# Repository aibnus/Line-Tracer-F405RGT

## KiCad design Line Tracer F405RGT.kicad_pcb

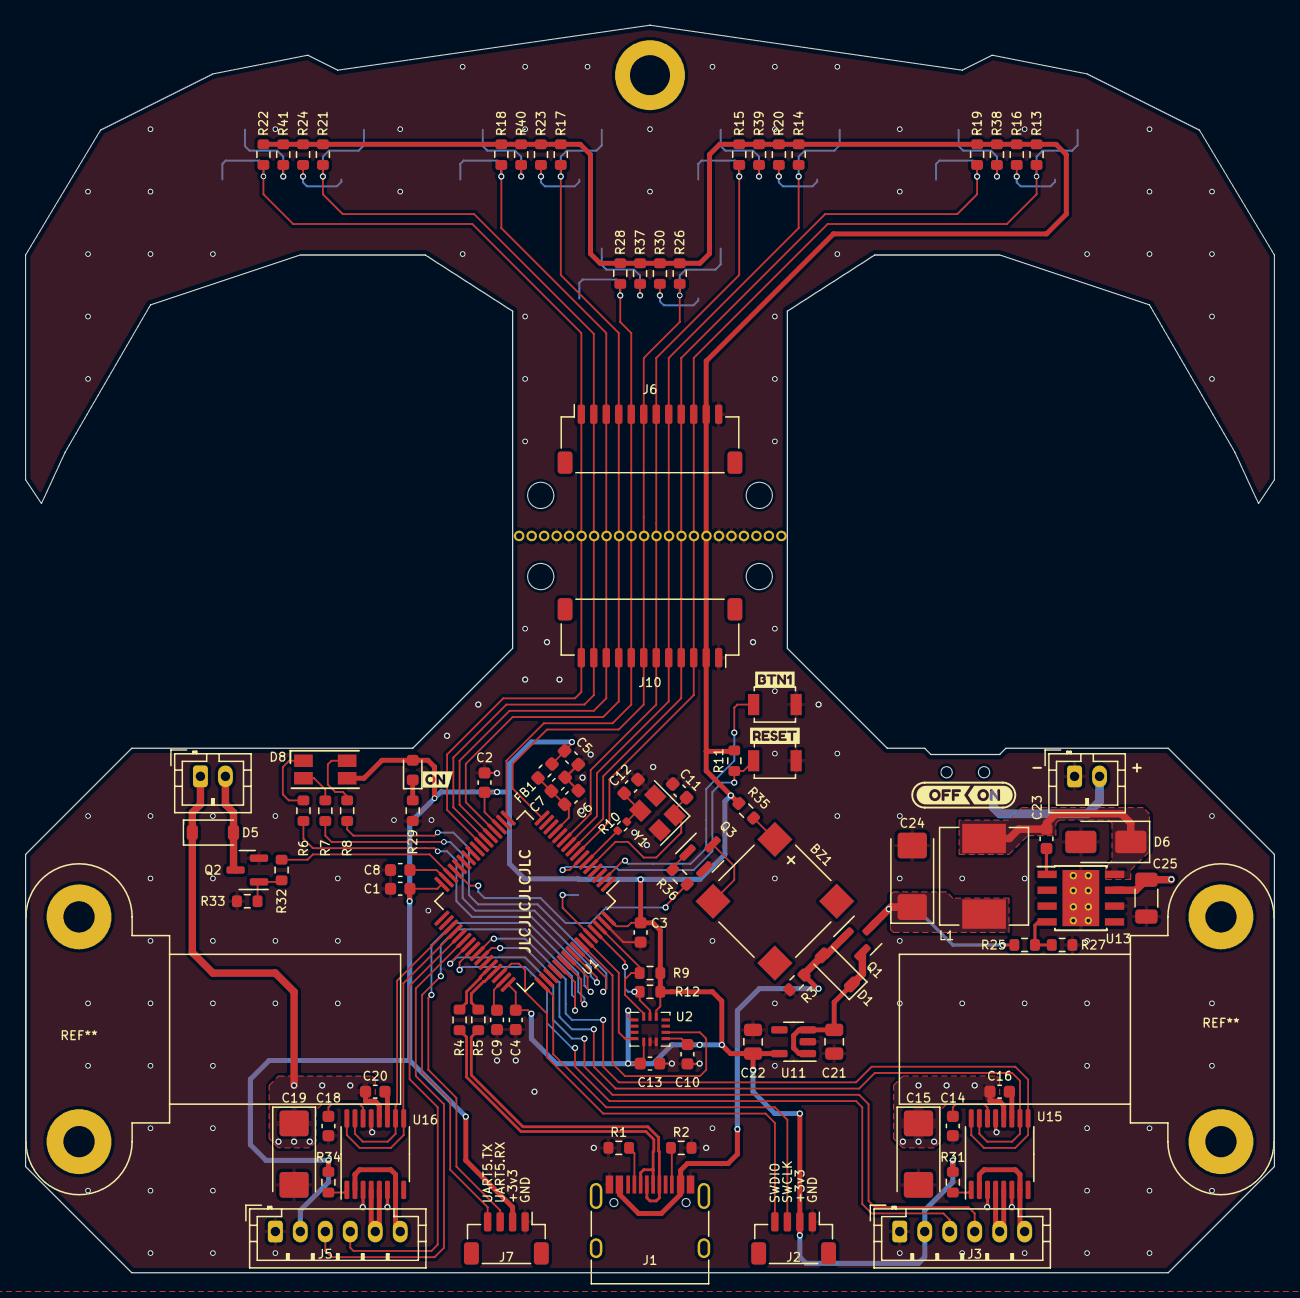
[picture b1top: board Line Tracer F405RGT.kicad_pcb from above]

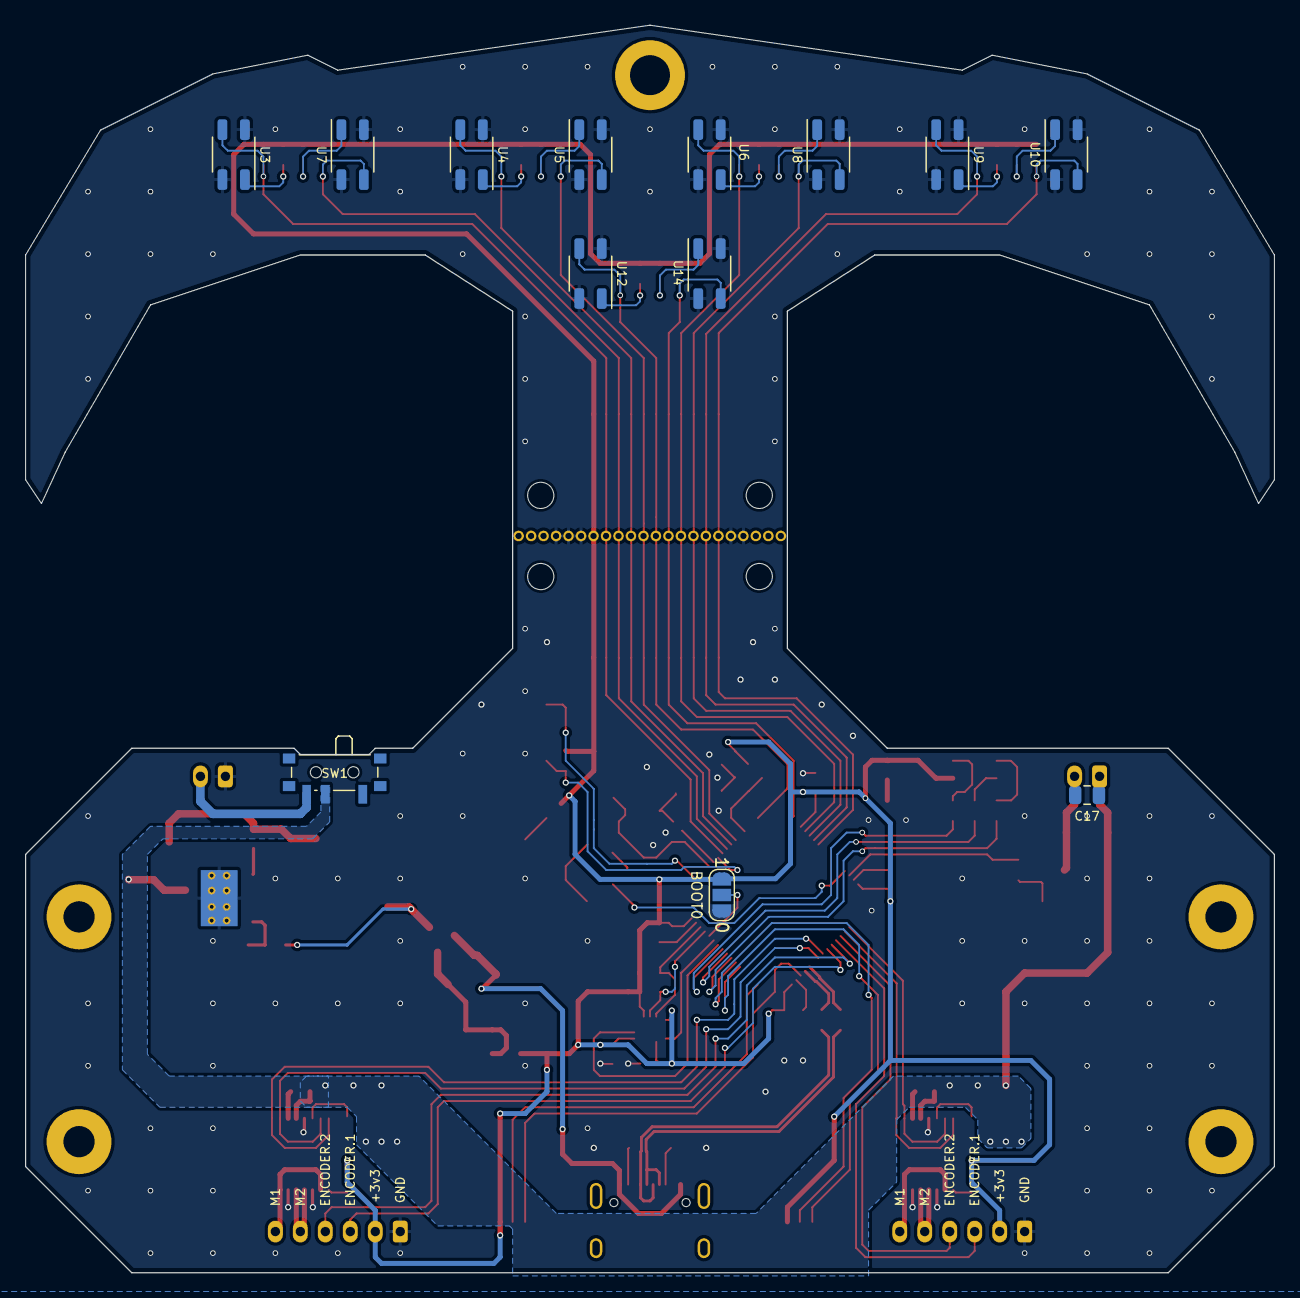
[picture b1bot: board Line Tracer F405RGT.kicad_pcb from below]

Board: 2 copper layers, 100.0 x 99.9 mm, 112 parts (13 on the bottom side), 85 nets.

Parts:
BZ1: Buzzer; PUIAudio_SMT_0825_S_4_R
C1, C6: 10u; C_0603_1608Metric
C2, C3, C4, C5, C10, C13: 100n; C_0603_1608Metric
C7, C16, C20, C23: 10n; C_0603_1608Metric
C8, C9: 2u2; C_0603_1608Metric
C11, C12: 12p; C_0603_1608Metric
C14, C18: 2.2u; C_0603_1608Metric
C15, C19: 10u; CP_EIA-6032-28_Kemet-C
C17: 100n; C_0805_2012Metric
C21, C22: 1u; C_0805_2012Metric
C24: 200u; CP_EIA-6032-28_Kemet-C
C25: 10u; C_1206_3216Metric
D1: 10V; D_SOD-123
D5: B5819W; D_SOD-123
D6: B340A; D_SMA
D7: red; LED_0603_1608Metric
D8: LED_RGAB; LED_RGB_1210
FB1: 600@600MHz; L_0603_1608Metric
J1: USB_C_Receptacle_USB2.0; USB_C_Receptacle_HRO_TYPE-C-31-M-12
J2, J7: Conn_01x04; JST_SH_BM04B-SRSS-TB_1x04-1MP_P1.00mm_Vertical
J3, J5: Conn_01x06; JST_PH_B6B-PH-K_1x06_P2.00mm_Vertical
J4, J9: Conn_01x02; JST_PH_B2B-PH-K_1x02_P2.00mm_Vertical
J6, J10: Conn_01x12; JST_SH_SM12B-SRSS-TB_1x12-1MP_P1.00mm_Horizontal
JP1: SolderJumper_3_Open; SolderJumper-3_P1.3mm_Open_RoundedPad1.0x1.5mm_NumberLabels
L1: 15u; L_Chilisin_BMRB00060650
Q1: AO3401A; SOT-23
Q2, Q3: AO3400A; SOT-23
R1, R2: 5k1; R_0603_1608Metric
R3, R9, R11, R12, R13, R14, R15, R17, R18, R19, R21, R22, R26, R28, R31, R33, R34: 47k; R_0603_1608Metric
R4, R5: 22; R_0603_1608Metric
R6, R7, R8, R29, R35: 1k; R_0603_1608Metric
R10: 47; R_0402_1005Metric
R16, R20, R23, R24, R30, R32, R36, R37, R38, R39, R40, R41: 120; R_0603_1608Metric
R25: 10k; R_0603_1608Metric
R27: 3k24; R_0603_1608Metric
SW1: SW_SPDT; SW_SPDT_PCM12
SW2: RESET; SW_SPST_B3U-1000P
SW3: BUTTON; SW_SPST_B3U-1000P
U1: STM32F405RGTx; LQFP-64_10x10mm_P0.5mm
U2: BMI160; Bosch_LGA-14_3x2.5mm_P0.5mm
U3, U4, U5, U6, U7, U8, U9, U10, U12, U14: ITR8307-S17-TR8; Everlight_ITR1201SR10AR
U11: AP2112K-3.3; SOT-23-5
U13: TPS5430DDA; TI_SO-PowerPAD-8_ThermalVias
U15, U16: DRV8833PW; TSSOP-16_4.4x5mm_P0.65mm
Y1: 16MHz; Crystal_SMD_3225-4Pin_3.2x2.5mm
kibuzzard-650E9EB5: G***; kibuzzard-650E9EB5
kibuzzard-650E9EBA: G***; kibuzzard-650E9EBA
kibuzzard-650E9EF6: G***; kibuzzard-650E9EF6
kibuzzard-650EFA42: G***; kibuzzard-650EFA42
kibuzzard-65119A4A: G***; kibuzzard-65119A4A

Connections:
+3.3VA: C6.1, C7.1, FB1.1, U1.13 (VDDA)
+3V3: C1.1, C2.1, C3.1, C4.1, C5.1, C10.1, C13.1, C22.1, D7.2 (A), D8.3 (A), FB1.2, J2.2, J3.2, J5.2, J6.11, J7.2, J10.2, JP1.1 (A), R9.1, R11.2, R12.1, R13.1, R14.1, R15.1, R16.1, R17.1, R18.1, R19.1, R20.1, R21.1, R22.1, R23.1, R24.1, R26.1, R28.1, R30.1, R31.1, R34.1, R35.1, R37.1, R38.1, R39.1, R40.1, R41.1, U1.19 (VDD), U1.32 (VDD), U1.48 (VDD), U1.64 (VDD), U2.1 (SDO), U2.5 (VDDIO), U2.8 (VDD), U2.12 (CSB), U11.5 (VOUT)
+5V: C24.1, L1.2, Q1.3 (D), R25.1
+BATT: J9.2, SW1.3 (C)
/MCU/BOOT0: JP1.2 (C), U1.60 (BOOT0)
/MCU/BUTTON: SW3.1, U1.2 (PC13)
/MCU/D1: J6.10, J10.3, R13.2, U1.8 (PC0), U3.3
/MCU/D2: J6.9, J10.4, R19.2, U1.9 (PC1), U7.3
/MCU/D3: J6.8, J10.5, R14.2, U1.10 (PC2), U4.3
/MCU/D4: J6.7, J10.6, R15.2, U1.11 (PC3), U5.3
/MCU/D5: J6.4, J10.9, R17.2, U1.20 (PA4), U6.3
/MCU/D6: J6.3, J10.10, R18.2, U1.21 (PA5), U8.3
/MCU/D7: J6.2, J10.11, R21.2, U1.22 (PA6), U9.3
/MCU/D8: J6.1, J10.12, R22.2, U1.23 (PA7), U10.3
/MCU/D_N: R4.1, U1.44 (PA11)
/MCU/D_P: R5.1, U1.45 (PA12)
/MCU/ENCODERA.1: J5.3, U1.38 (PC7)
/MCU/ENCODERA.2: J5.4, U1.37 (PC6)
/MCU/ENCODERB.1: J3.3, U1.40 (PC9)
/MCU/ENCODERB.2: J3.4, U1.39 (PC8)
/MCU/HSE_IN: C11.1, U1.5 (PH0), Y1.1
/MCU/HSE_OUT: R10.1, U1.6 (PH1)
/MCU/INT1: U1.58 (PB6), U2.9 (INT2)
/MCU/INT2: U1.59 (PB7), U2.4 (INT1)
/MCU/LED1: R6.1, U1.55 (PB3)
/MCU/LED2: R7.1, U1.56 (PB4)
/MCU/LED3: R8.1, U1.57 (PB5)
/MCU/MD3: J6.6, J10.7, R26.2, U1.16 (PA2), U12.3
/MCU/MD4: J6.5, J10.8, R28.2, U1.17 (PA3), U14.3
/MCU/PWMA.1: U1.35 (PB14), U16.10 (BIN2), U16.15 (AIN2)
/MCU/PWMA.2: U1.36 (PB15), U16.9 (BIN1), U16.16 (AIN1)
/MCU/PWMB.1: U1.41 (PA8), U15.9 (BIN1), U15.16 (AIN1)
/MCU/PWMB.2: U1.42 (PA9), U15.10 (BIN2), U15.15 (AIN2)
/MCU/PWM_AUX: R32.2, U1.30 (PB11)
/MCU/RST: R11.1, SW2.1, U1.7 (NRST)
/MCU/RX5: J7.3, U1.54 (PD2)
/MCU/SCL: R12.2, U1.61 (PB8), U2.13 (SCx)
/MCU/SDA: R9.2, U1.62 (PB9), U2.14 (SDx)
/MCU/SWCLK: J2.3, U1.49 (PA14)
/MCU/SWDIO: J2.4, U1.46 (PA13)
/MCU/TX5: J7.4, U1.53 (PC12)
/MCU/USB_N: J1.A7 (D-), J1.B7 (D-), R4.2
/MCU/USB_P: J1.A6 (D+), J1.B6 (D+), R5.2
/Power/VSENSE: R25.2, R27.1, U13.4 (VSENSE)
GND: C1.2, C2.2, C3.2, C4.2, C5.2, C6.2, C7.2, C8.2, C9.2, C10.2, C11.2, C12.2, C13.2, C14.2, C15.2, C18.2, C19.2, C21.2, C22.2, C24.2, C25.2, D6.2 (A), J1.A1 (GND), J1.A12 (GND), J1.B1 (GND), J1.B12 (GND), J2.1, J3.1, J5.1, J6.12, J7.1, J9.1, J10.1, JP1.3 (B), Q2.2 (S), Q3.2 (S), R1.1, R2.1, R3.2, R27.2, R29.1, R33.2, SW2.2, SW3.2, U1.12 (VSSA), U1.18 (VSS), U1.63 (VSS), U2.6 (GNDIO), U2.7 (GND), U3.1 (K), U3.4, U4.1 (K), U4.4, U5.1 (K), U5.4, U6.1 (K), U6.4, U7.1 (K), U7.4, U8.1 (K), U8.4, U9.1 (K), U9.4, U10.1 (K), U10.4, U11.2 (GND), U12.1 (K), U12.4, U13.6 (GND), U13.9 (GNDPAD), U14.1 (K), U14.4, U15.3 (AISEN), U15.6 (BISEN), U15.13 (GND), U16.3 (AISEN), U16.6 (BISEN), U16.13 (GND), Y1.2, Y1.4
unnamed: BZ1.2 (+), Q3.3 (D)
unnamed: BZ1.1 (-), R35.2
unnamed: C12.1, R10.2, Y1.3
unnamed: C17.2, D5.2 (A), J4.2, Q2.3 (D)
unnamed: C23.2, D6.1 (K), L1.1, U13.8 (PH)
unnamed: D7.1 (K), R29.2
unnamed: D8.4 (BK), R8.2
unnamed: D8.2 (GK), R7.2
unnamed: D8.1 (RK), R6.2
unnamed: J1.A5 (CC1), R1.2
unnamed: J1.B5 (CC2), R2.2
unnamed: J3.5, U15.4 (AOUT2), U15.5 (BOUT2)
unnamed: J3.6, U15.2 (AOUT1), U15.7 (BOUT1)
unnamed: J5.5, U16.4 (AOUT2), U16.5 (BOUT2)
unnamed: J5.6, U16.2 (AOUT1), U16.7 (BOUT1)
unnamed: Q2.1 (G), R32.1, R33.1
unnamed: Q3.1 (G), R36.2
unnamed: R36.1, U1.29 (PB10)
unnamed: C8.1, U1.31 (VCAP_1)
unnamed: C9.1, U1.47 (VCAP_2)
unnamed: R16.2, U3.2 (A)
unnamed: R20.2, U4.2 (A)
unnamed: R39.2, U5.2 (A)
unnamed: R23.2, U6.2 (A)
unnamed: R38.2, U7.2 (A)
unnamed: R40.2, U8.2 (A)
unnamed: R24.2, U9.2 (A)
unnamed: R41.2, U10.2 (A)
unnamed: R30.2, U12.2 (A)
unnamed: C23.1, U13.1 (BOOT)
unnamed: R37.2, U14.2 (A)
unnamed: C16.2, U15.11 (VCP)
unnamed: C14.1, U15.14 (VINT)
unnamed: R31.2, U15.1 (nSLEEP)
unnamed: C20.2, U16.11 (VCP)
unnamed: C18.1, U16.14 (VINT)
unnamed: R34.2, U16.1 (nSLEEP)
VBUS: D1.2 (A), J1.A4 (VBUS), J1.A9 (VBUS), J1.B4 (VBUS), J1.B9 (VBUS), Q1.1 (G), R3.1
VDD: C21.1, D1.1 (K), Q1.2 (S), U11.1 (VIN), U11.3 (EN)
V_BATT: C15.1, C16.1, C17.1, C19.1, C20.1, C25.1, D5.1 (K), J4.1, SW1.2 (B), U13.7 (VIN), U15.12 (VM), U16.12 (VM)

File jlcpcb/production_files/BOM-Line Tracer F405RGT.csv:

Comment,Designator,Footprint,LCSC
16MHz,Y1,Crystal_SMD_3225-4Pin_3.2x2.5mm,C13738
100n,"C10,C13,C2,C3,C4,C5",C_0603_1608Metric,C14663
1k,"R29,R35,R6,R7,R8",R_0603_1608Metric,C21190
120,"R16,R20,R23,R24,R30,R32,R36,R37,R38,R39,R40,R41",R_0603_1608Metric,C22787
5k1,"R1,R2",R_0603_1608Metric,C23186
22,"R4,R5",R_0603_1608Metric,C23345
2.2u,"C14,C18,C8,C9",C_0603_1608Metric,C23630
47,R10,R_0402_1005Metric,C25120
47k,"R11,R12,R13,R14,R15,R17,R18,R19,R21,R22,R26,R28,R3,R31,R33,R34,R9",R_0603_1608Metric,C25819
1u,"C21,C22",C_0805_2012Metric,C28323
15u,L1,L_Chilisin_BMRB00060650,C3002651
12p,"C11,C12",C_0603_1608Metric,C38523
10n,"C16,C20,C23,C7",C_0603_1608Metric,C57112
BMI160,U2,Bosch_LGA-14_3x2.5mm_P0.5mm,C94021
10u,"C1,C6",C_0603_1608Metric,C96446
TPS5430DDA,U13,TI_SO-PowerPAD-8_ThermalVias,C9864
AO3400A,Q3,SOT-23,
DRV8833PW,U16,TSSOP-16_4.4x5mm_P0.65mm,
DRV8833PW,U15,TSSOP-16_4.4x5mm_P0.65mm,
600@600MHz,FB1,L_0603_1608Metric,
10u,C19,CP_EIA-6032-28_Kemet-C,
blue,D4,LED_0603_1608Metric,
200u,C24,CP_EIA-6032-28_Kemet-C,
10u,C25,C_1206_3216Metric,
3k24,R27,R_0603_1608Metric,
AO3401A,Q1,SOT-23,
10k,R25,R_0603_1608Metric,
Buzzer,BZ1,PUIAudio_SMT_0825_S_4_R,
yellow,D3,LED_0603_1608Metric,
10V,D1,D_SOD-123,
STM32F405RGTx,U1,LQFP-64_10x10mm_P0.5mm,
B5819W,D5,D_SOD-123,
red,D7,LED_0603_1608Metric,
AP2112K-3.3,U11,SOT-23-5,
AO3400A,Q2,SOT-23,
green,D2,LED_0603_1608Metric,
10u,C15,CP_EIA-6032-28_Kemet-C,
B340A,D6,D_SMA,
100n,C17,C_0805_2012Metric,

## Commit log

2023-11-01 improved sensor design
